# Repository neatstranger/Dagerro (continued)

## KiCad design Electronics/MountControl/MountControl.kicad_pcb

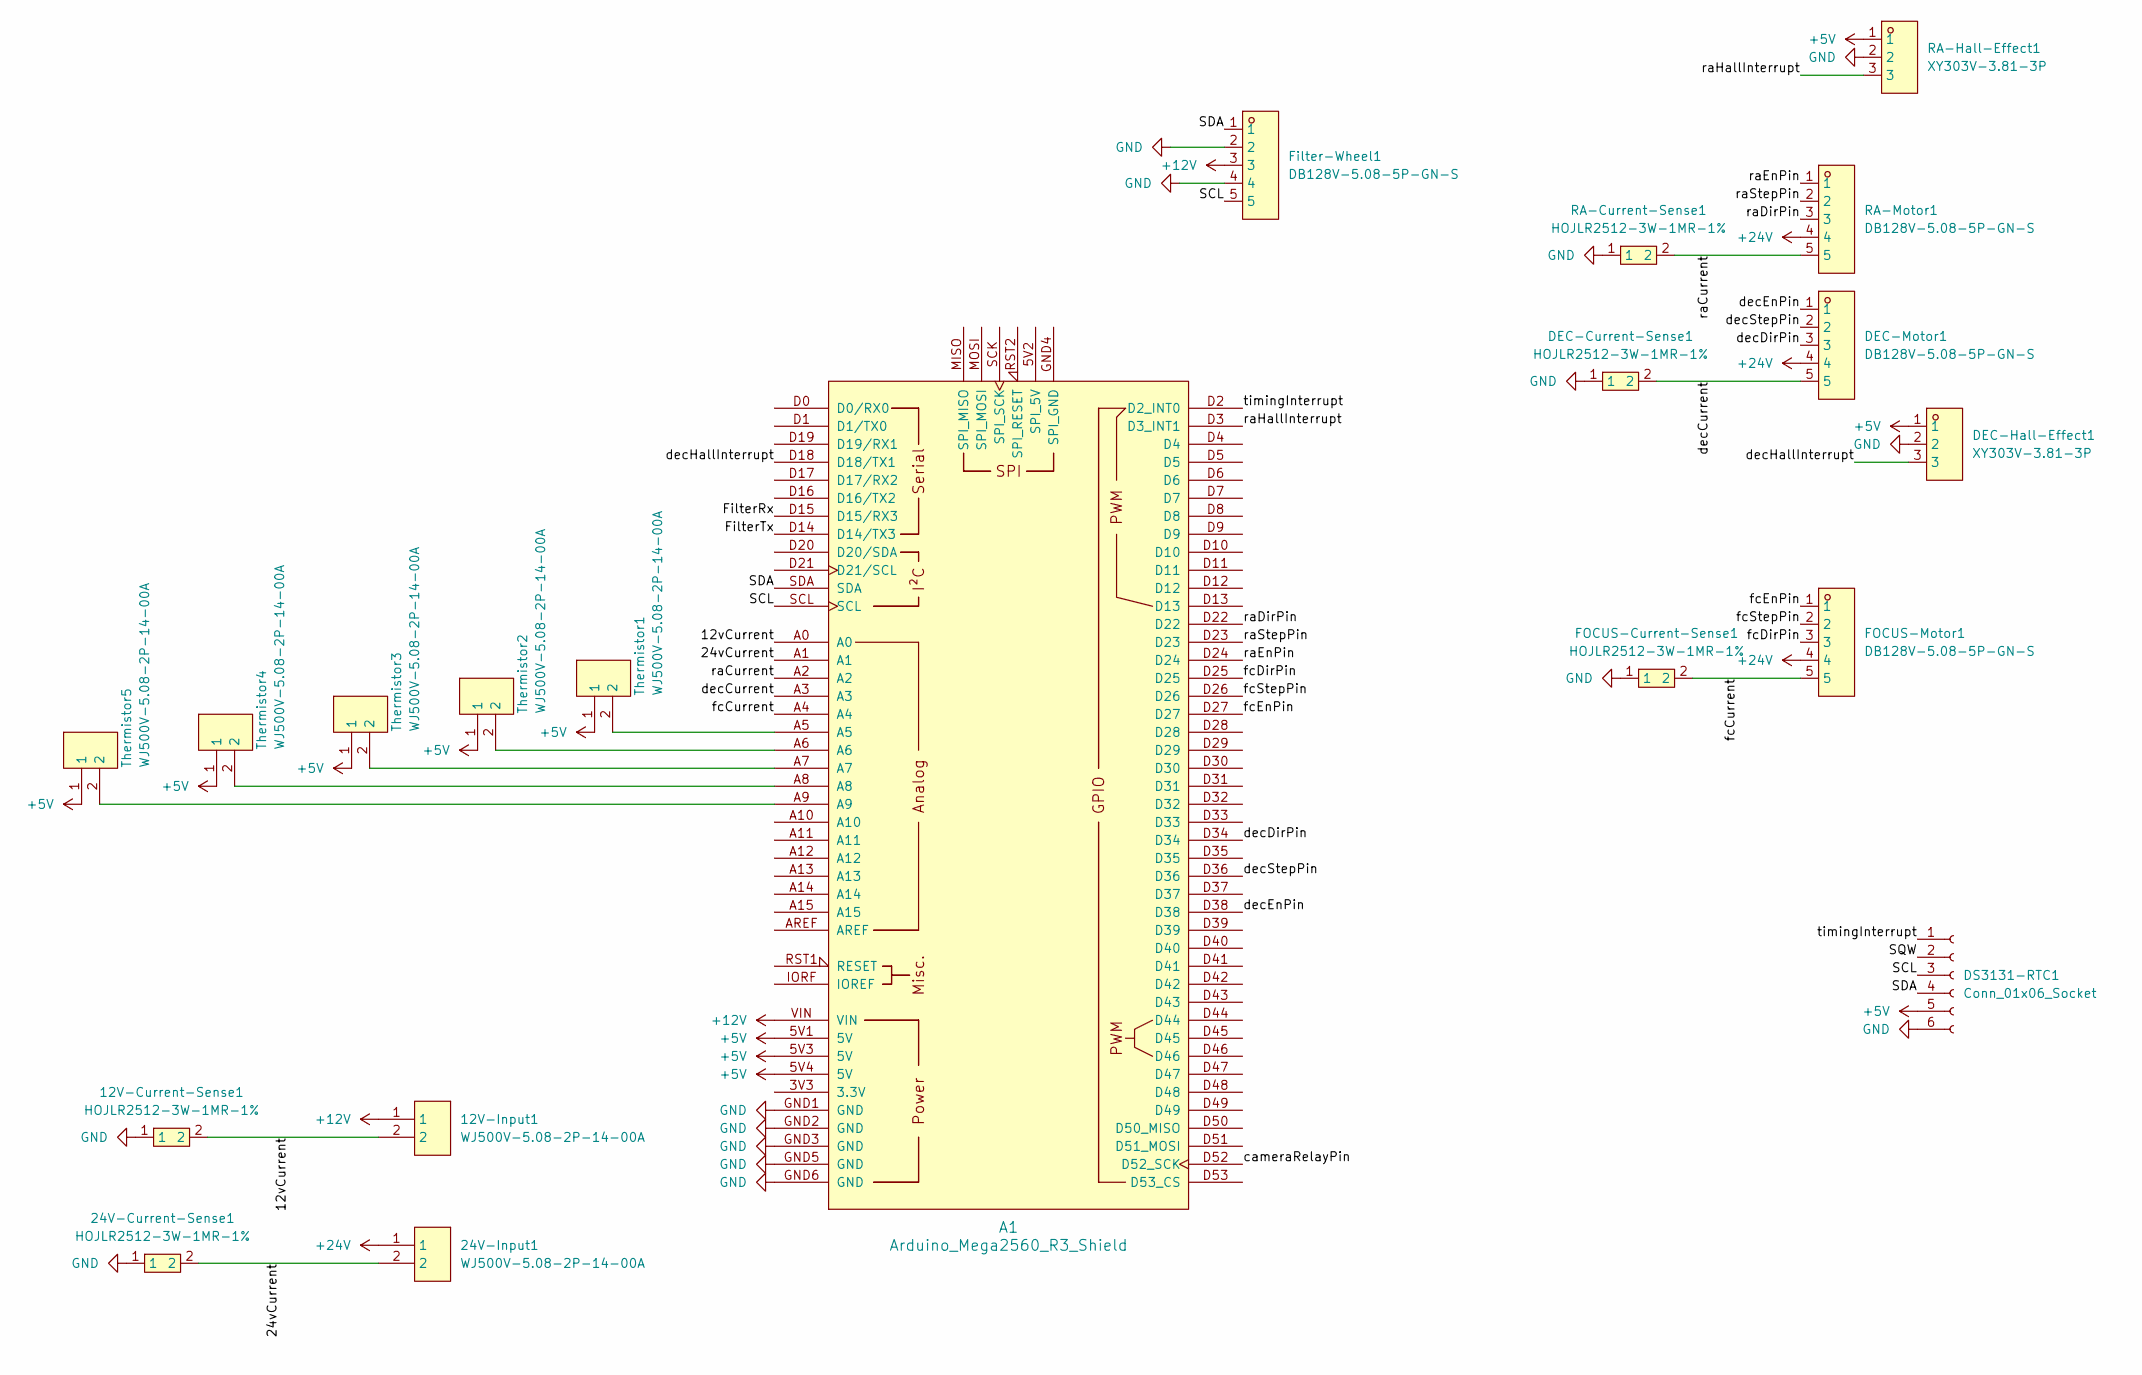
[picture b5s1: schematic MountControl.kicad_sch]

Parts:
12V-Current-Sense1, 24V-Current-Sense1: HOJLR2512-3W-1MR-1%; RES-SMD_L6.4-W3.2-R2512; LCSC Part C2903470
12V-Input1, 24V-Input1: WJ500V-5.08-2P-14-00A; CONN-TH_2P-P5.00_WJ500V-5.08-2P; LCSC Part C8465
A1: Arduino_Mega2560_R3_Shield
DEC-Current-Sense1: HOJLR2512-3W-1MR-1%; RES-SMD_L6.4-W3.2-R2512; LCSC Part C2903470
DEC-Hall-Effect1: XY303V-3.81-3P; CONN-TH_XY303V-3.81-3P; LCSC Part C557684
DEC-Motor1: DB128V-5.08-5P-GN-S; CONN-TH_5P-P5.08_DIBO_DB128V-5.08-5P-GN-S; LCSC Part C2927513
DS3131-RTC1: Conn_01x06_Socket; PinHeader_1x06_P2.54mm_Horizontal
FOCUS-Current-Sense1: HOJLR2512-3W-1MR-1%; RES-SMD_L6.4-W3.2-R2512; LCSC Part C2903470
FOCUS-Motor1: DB128V-5.08-5P-GN-S; CONN-TH_5P-P5.08_DIBO_DB128V-5.08-5P-GN-S; LCSC Part C2927513
Filter-Wheel1: DB128V-5.08-5P-GN-S; CONN-TH_5P-P5.08_DIBO_DB128V-5.08-5P-GN-S; LCSC Part C2927513
RA-Current-Sense1: HOJLR2512-3W-1MR-1%; RES-SMD_L6.4-W3.2-R2512; LCSC Part C2903470
RA-Hall-Effect1: XY303V-3.81-3P; CONN-TH_XY303V-3.81-3P; LCSC Part C557684
RA-Motor1: DB128V-5.08-5P-GN-S; CONN-TH_5P-P5.08_DIBO_DB128V-5.08-5P-GN-S; LCSC Part C2927513
Thermistor1, Thermistor2, Thermistor3, Thermistor4, Thermistor5: WJ500V-5.08-2P-14-00A; CONN-TH_2P-P5.00_WJ500V-5.08-2P; LCSC Part C8465

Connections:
+5V: A1.5V1 (5V), A1.5V3 (5V), A1.5V4 (5V), DEC-Hall-Effect1.1, DS3131-RTC1.5, RA-Hall-Effect1.1, Thermistor1.1, Thermistor2.1, Thermistor3.1, Thermistor4.1, Thermistor5.1
+12V: 12V-Input1.1, A1.VIN, Filter-Wheel1.3
+24V: 24V-Input1.1, DEC-Motor1.4, FOCUS-Motor1.4, RA-Motor1.4
/12vCurrent: 12V-Current-Sense1.2, 12V-Input1.2, A1.A0
/24vCurrent: 24V-Current-Sense1.2, 24V-Input1.2, A1.A1
/FilterRx: A1.D15 (D15/RX3)
/FilterTx: A1.D14 (D14/TX3)
/SCL: A1.SCL, DS3131-RTC1.3, Filter-Wheel1.5
/SDA: A1.SDA, DS3131-RTC1.4, Filter-Wheel1.1
/SQW: DS3131-RTC1.2
/cameraRelayPin: A1.D52 (D52_SCK)
/decCurrent: A1.A3, DEC-Current-Sense1.2, DEC-Motor1.5
/decDirPin: A1.D34, DEC-Motor1.3
/decEnPin: A1.D38, DEC-Motor1.1
/decHallInterrupt: A1.D18 (D18/TX1), DEC-Hall-Effect1.3
/decStepPin: A1.D36, DEC-Motor1.2
/fcCurrent: A1.A4, FOCUS-Current-Sense1.2, FOCUS-Motor1.5
/fcDirPin: A1.D25, FOCUS-Motor1.3
/fcEnPin: A1.D27, FOCUS-Motor1.1
/fcStepPin: A1.D26, FOCUS-Motor1.2
/raCurrent: A1.A2, RA-Current-Sense1.2, RA-Motor1.5
/raDirPin: A1.D22, RA-Motor1.3
/raEnPin: A1.D24, RA-Motor1.1
/raHallInterrupt: A1.D3 (D3_INT1), RA-Hall-Effect1.3
/raStepPin: A1.D23, RA-Motor1.2
/timingInterrupt: A1.D2 (D2_INT0), DS3131-RTC1.1
GND: 12V-Current-Sense1.1, 24V-Current-Sense1.1, A1.GND1 (GND), A1.GND2 (GND), A1.GND3 (GND), A1.GND5 (GND), A1.GND6 (GND), DEC-Current-Sense1.1, DEC-Hall-Effect1.2, DS3131-RTC1.6, FOCUS-Current-Sense1.1, Filter-Wheel1.2, Filter-Wheel1.4, RA-Current-Sense1.1, RA-Hall-Effect1.2
unnamed: A1.A5, Thermistor1.2
unnamed: A1.A6, Thermistor2.2
unnamed: A1.A7, Thermistor3.2
unnamed: A1.A8, Thermistor4.2
unnamed: A1.A9, Thermistor5.2

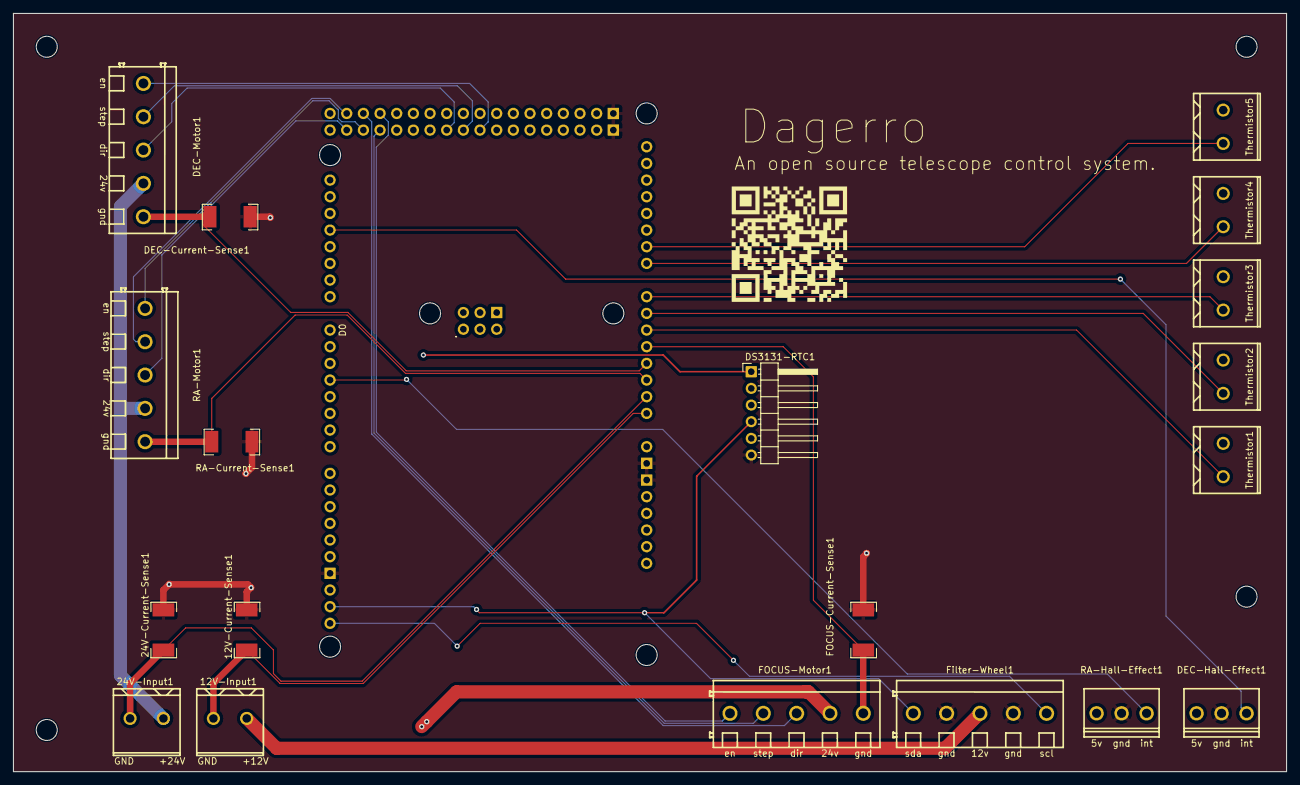
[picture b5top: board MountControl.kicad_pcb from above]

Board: 4 copper layers, 194.1 x 115.6 mm, 20 parts (0 on the bottom side), 28 nets.

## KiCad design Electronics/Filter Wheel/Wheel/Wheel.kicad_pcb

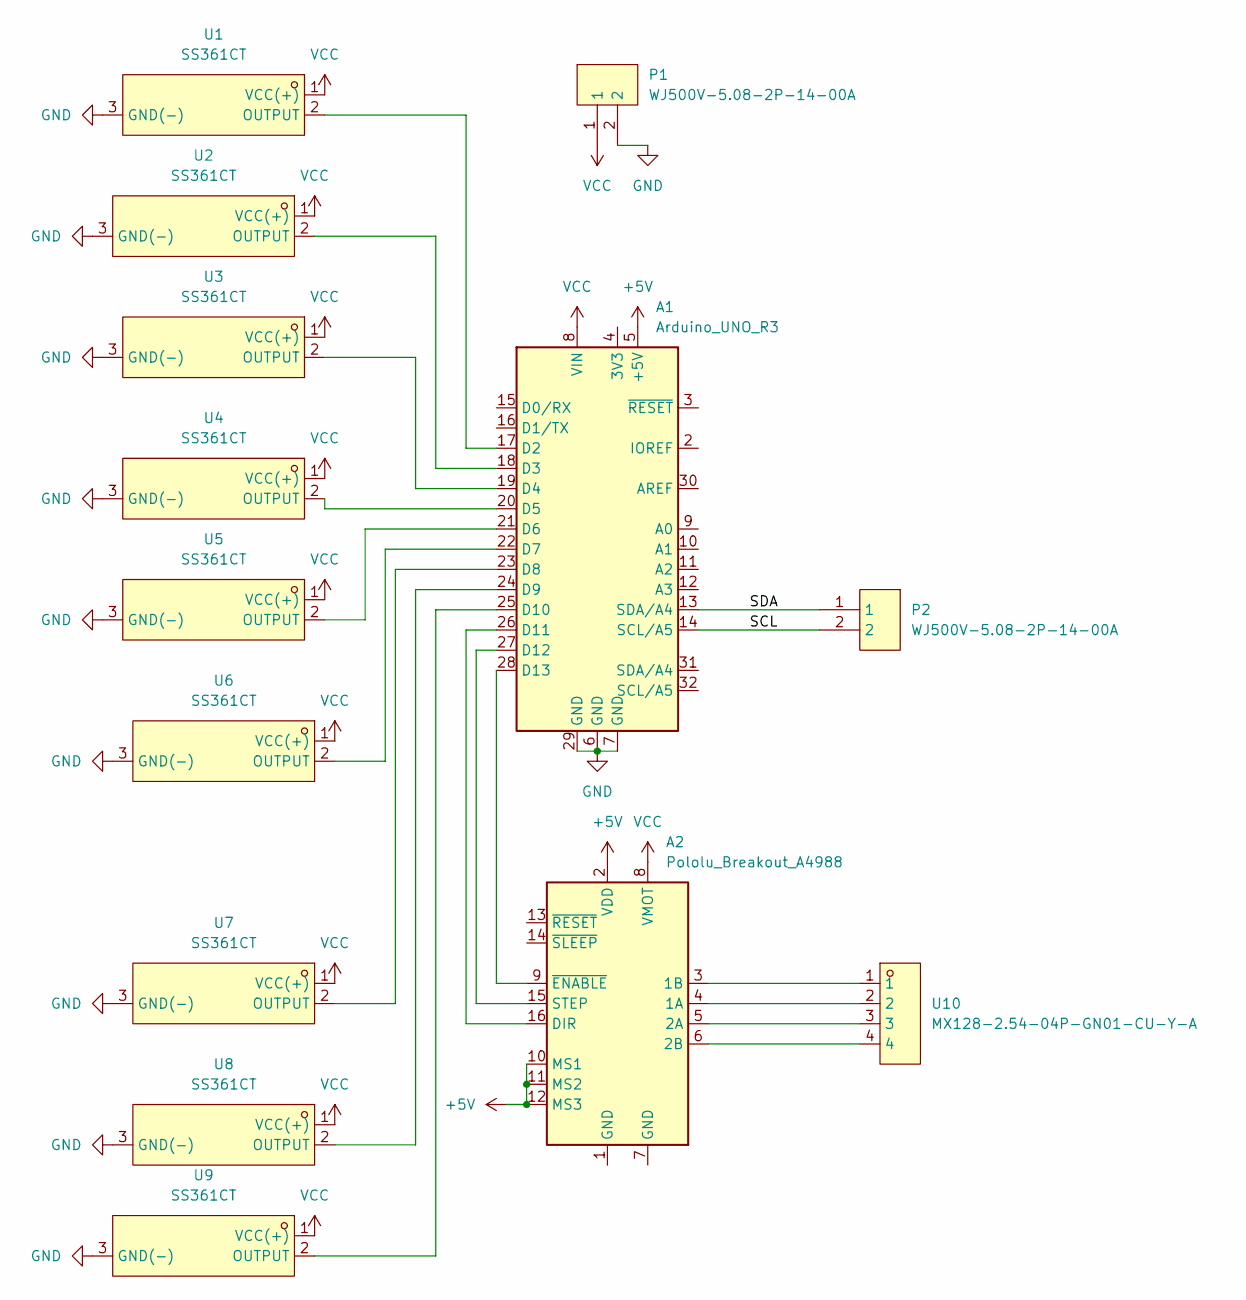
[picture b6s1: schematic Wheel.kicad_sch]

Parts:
A1: Arduino_UNO_R3
A2: Pololu_Breakout_A4988; Pololu_Breakout-16_15.2x20.3mm
P1, P2: WJ500V-5.08-2P-14-00A; CONN-TH_2P-P5.00_WJ500V-5.08-2P; LCSC Part C8465
U1, U2, U3, U4, U5, U6, U7, U8, U9: SS361CT; SOT-23-3_L2.9-W1.3-P1.90-LS2.4-BR; LCSC Part C396072
U10: MX128-2.54-04P-GN01-CU-Y-A; CONN-TH_4P-P2.54_MX128-2.54-GN01-04P-CU-Y-A; LCSC Part C5188444

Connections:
+5V: A1.5 (+5V), A2.2 (VDD), A2.10 (MS1), A2.11 (MS2), A2.12 (MS3)
/SCL: A1.14 (SCL/A5), P2.2
/SDA: A1.13 (SDA/A4), P2.1
GND: A1.6 (GND), A1.7 (GND), A1.29 (GND), P1.2, U1.3 (GND(-)), U2.3 (GND(-)), U3.3 (GND(-)), U4.3 (GND(-)), U5.3 (GND(-)), U6.3 (GND(-)), U7.3 (GND(-)), U8.3 (GND(-)), U9.3 (GND(-))
unnamed: A1.17 (D2), U1.2 (OUTPUT)
unnamed: A1.18 (D3), U2.2 (OUTPUT)
unnamed: A1.19 (D4), U3.2 (OUTPUT)
unnamed: A1.20 (D5), U4.2 (OUTPUT)
unnamed: A1.21 (D6), U5.2 (OUTPUT)
unnamed: A1.22 (D7), U6.2 (OUTPUT)
unnamed: A1.23 (D8), U7.2 (OUTPUT)
unnamed: A1.24 (D9), U8.2 (OUTPUT)
unnamed: A1.25 (D10), U9.2 (OUTPUT)
unnamed: A1.26 (D11), A2.16 (DIR)
unnamed: A1.27 (D12), A2.15 (STEP)
unnamed: A1.28 (D13), A2.9 (~ENABLE)
unnamed: A2.4 (1A), U10.2
unnamed: A2.3 (1B), U10.1
unnamed: A2.5 (2A), U10.3
unnamed: A2.6 (2B), U10.4
VCC: A1.8 (VIN), A2.8 (VMOT), P1.1, U1.1 (VCC(+)), U2.1 (VCC(+)), U3.1 (VCC(+)), U4.1 (VCC(+)), U5.1 (VCC(+)), U6.1 (VCC(+)), U7.1 (VCC(+)), U8.1 (VCC(+)), U9.1 (VCC(+))

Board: 2 copper layers, 14 parts (0 on the bottom side), 21 nets, no tracks yet.

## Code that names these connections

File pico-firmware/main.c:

#include <stdio.h>
#include <stdlib.h>
#include "pico/stdlib.h"
#include "hardware/i2c.h"

#include "i2c.h"

#define RTC_ADDR 32
#define KHZ 13
#define EN_5V 14
#define EN_CAM 15

#define EN_DEC 6
#define STEP_DEC 7
#define DIR_DEC 8

#define EN_EQ 10 
#define STEP_EQ 11
#define DIR_EQ 12

#define EN_FC 20
#define STEP_FC 19
#define DIR_FC 18


#define HOME_EQ 2
#define HOME_DEC 3

/*#define TRK_DIR 1 */
#define STEP_SLEEP_US 500



#define SMALL_CT_LOOPS 776
#define SMALL_CT_PULSES 1485

#define LG_CT_LOOPS 724
#define LG_CT_PULSES 1486

int currentInterrupts = 0;
bool onLGLoop = false;
int loops = 0;
int decComp = 100;
bool decCompDir = false;
bool decCompEnabled = false;

bool trackingEnabled = true;
bool TRK_DIR = false;


int initializeIo(){
	int controlPins[] = {EN_5V, EN_CAM, EN_DEC, STEP_DEC, DIR_DEC, EN_EQ, STEP_EQ, DIR_EQ, EN_FC, STEP_FC, DIR_FC};
	int numPins  = sizeof(controlPins) / sizeof(controlPins[0]);
	for(int i = 0; i < numPins; i++){
		printf("Initiated Pin # %d \n", controlPins[i]);
		gpio_init(controlPins[i]);
		gpio_set_dir(controlPins[i], GPIO_OUT);
	}
	gpio_init(KHZ);
	gpio_set_dir(KHZ, GPIO_IN);
	
	gpio_init(HOME_EQ);
	gpio_init(HOME_DEC);

	gpio_set_dir(HOME_EQ, GPIO_IN);
	gpio_set_dir(HOME_DEC, GPIO_IN);
	gpio_pull_up(HOME_EQ);
	gpio_pull_up(HOME_DEC);
	return 0;
		
}


int moveDecAxis(bool dir, long int steps){
	gpio_put(DIR_DEC, dir);
	busy_wait_us_32(100);
	for(long int i = 0; i < steps; i++){
		gpio_put(STEP_DEC, 1);
		busy_wait_us_32(STEP_SLEEP_US);
		gpio_put(STEP_DEC, 0);
	}
	return 0;
}
int moveEQAxis(bool dir, long int steps){
	gpio_put(DIR_EQ, dir);
	busy_wait_us_32(100);
	for(long int i = 0; i < steps; i++){
		gpio_put(STEP_EQ, 1);
		busy_wait_us_32(STEP_SLEEP_US);
		gpio_put(STEP_EQ, 0);
	}
	return 0;
}
int moveFocAxis(bool dir, long int steps){
	gpio_put(DIR_FC, dir);
	for(long int i = 0; i < steps; i++){
		gpio_put(STEP_FC, 1);
		busy_wait_us_32(STEP_SLEEP_US);
		gpio_put(STEP_FC, 0);
	}
	return 0;
}

void callBack(uint gpio, uint32_t events){
	if(trackingEnabled){
		currentInterrupts += 1;
		if(onLGLoop){
			if(currentInterrupts == LG_CT_PULSES-1){
				currentInterrupts = 0;
				moveEQAxis(TRK_DIR, 1);
				loops += 1;
				if(loops % decComp && decCompEnabled){
					moveDecAxis(decCompDir, decComp);
				}
				if(loops == LG_CT_LOOPS-1){
					onLGLoop = false;
					loops = 0;
					printf("LoopReset\n");
				}
			}
		}else{
			if(currentInterrupts == SMALL_CT_PULSES -1){
				currentInterrupts = 0;
				moveEQAxis(TRK_DIR, 1);
				loops +=1;
				if (loops % decComp && decCompEnabled){
					moveDecAxis(decCompDir, decComp);
				}
				if(loops == SMALL_CT_LOOPS -1){
					loops = 0;
					onLGLoop = true;
					printf("LoopReset \n");
				}
			}
		}
	}
}
int char_array_to_int(const char *chars, int length) {
    int result = 0;
    int is_negative = 0;
    int start = 0;

    // Check if the number is negative
    if (chars[0] == '-') {
        is_negative = 1;
        start = 1; // Start from the next character
    }

    for (int i = start; i < length; i++) {
        // Shift the result by 1 decimal place (multiply by 10)
        result = (result << 3) + (result << 1); // result * 10 using bit shifting

        // Convert the current character to its integer value and add it
        result += chars[i] - '0';
    }

    // Apply the negative sign if needed
    if (is_negative) {
        result = -result;
    }

    return result;
}
int executeMoveCommand(int eq, int dec, int fc){
	trackingEnabled = false;
	printf("Disabled Tracking For Manual Control\n......\n");
	if(eq == 0){
		printf("No EQ Command\n");
	}else if(eq != 0){
		printf("Moving EQ Axis %d steps, in the %d direction \n", abs(eq), eq > 0);
		moveEQAxis(eq > 0, abs(eq));
	}
	if(dec == 0){
		printf("No DEC Command\n");
	}else if (dec != 0){
		printf("Moving DEC Axis %d steps, in the %d direction \n", abs(dec), dec >0);
		moveDecAxis(dec > 0, abs(dec));
	}
	if(fc == 0){
		printf("No Focus Command\n");
	}else if( fc != 0){
		printf("Moving FC Axis %d steps, in the %d direction \n", abs(fc), fc >0);
		moveFocAxis(fc > 0, abs(fc));
	}

	printf(".....\nFinished all movement commands, re-enabling tracking ...\n");
	trackingEnabled = true;

	
}
int executeMachineCommand(int commandNumber){
	printf("Machine command %d  initiated \n", commandNumber);
	if(commandNumber == 1){
		printf("Disabling Steppers and Tracking\n");
		gpio_put(EN_EQ, 0);
		gpio_put(EN_DEC, 0);
		gpio_put(EN_FC, 0);
		trackingEnabled = false;
	}else if(commandNumber == 2){
		printf("Enabling All Axis");
		gpio_put(EN_EQ, 1);
		gpio_put(EN_DEC, 1);
		gpio_put(EN_FC, 1);
	}else if(commandNumber == 3){
		trackingEnabled = true;
	}else if (commandNumber ==4){
		gpio_put(EN_CAM, 0);
		sleep_ms(50);
		gpio_put(EN_CAM, 1);
	}else if (commandNumber == 5){
		TRK_DIR = !TRK_DIR;
	}else if (commandNumber == 6){
		decComp += 10;
	}else if (commandNumber == 6){
		decComp -= 10;
	}else if (commandNumber == 7){
		decCompDir = !decCompDir;
	}else if (commandNumber == 8){
		decCompEnabled = !decCompEnabled;
	}

	return 0;

}
int main(){
	stdio_init_all();
	printf("Initializing...\n");
	initializeI2C();
	initializeIo();
	gpio_put(EN_CAM, 1);
	gpio_put(EN_DEC, 1);
	gpio_put(EN_EQ, 1);
	gpio_put(EN_FC, 1);
	gpio_set_irq_enabled_with_callback(KHZ, 0x04, 1, & callBack);
	executeMachineCommand(3);
	bool messageCompleted = false;
	char message[1000];	
	int messageChar = 0;
	int cmds[3];
	printf("Tracking Enabled: %d \n", trackingEnabled);
	while(1){
		if(!gpio_get(HOME_EQ)){
			printf("EQ IS HOMED \n");
		}
		if(!gpio_get(HOME_DEC)){
			printf("DEC IS HOMED \n");
		}
		if(uart_is_readable(uart0)){
			char c = uart_getc(uart0);
			message[messageChar] = c;
			messageChar += 1;
			if(c == '\r'){
				messageCompleted = true;
				message[messageChar -1] = 0;
				messageChar = 0;
			}
		}
		if(messageCompleted && message[0] != 'G'){
			int count = 0; 
			char numArr[1000];
			int varsPulled = 0;
			for(int i = 0; i < 1000; i++){
				if(message[i] != 0 || varsPulled < 3){
					if(message[i] != ';'){
						numArr[count] = message[i];
						count++;
					}else{
						cmds[varsPulled] = char_array_to_int(numArr, count);								  varsPulled += 1;
						count = 0;
						for(int i = 0; i < 1000; i++){
							numArr[i] = 0; 
						}
					}
				}
			}	
			messageCompleted = false;
			executeMoveCommand(cmds[0], cmds[1], cmds[2]);
			for (int i = 0; i < 1000; i++){
				message[i] = 0;
			}
			cmds[0] = 0;
			cmds[1] = 0;
			cmds[2] = 0;
		}else if(messageCompleted){
			int count = 0;
			char numArr[1000];
			for (int i = 1; i < 1000; i++){
				if(message[i] != 0){
					numArr[count] = message[i];
					count++;
				}else{
					numArr[i] = message[i];
			}
		}
				
			executeMachineCommand(char_array_to_int(numArr, count));
			messageCompleted = false;
			for (int i = 0; i < 1000; i++){
				message[i] = 0;
				numArr[i] = 0;
			}


	}	

	}
    
}

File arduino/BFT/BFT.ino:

#include <DS3231.h>
DS3231 RTC;



//RTC Pins
const uint8_t timingInterruptPin = 2; //Hardware interrupt 4
//Hall Effect Sensor Pins
const uint8_t eqHallInterruptPin = 3;//Eq
const uint8_t decHallInterruptPin = 18;//Dec
//DEC Stepper Pins
const uint8_t decEnPin = 38;// Enable 22
const uint8_t decStepPin = 36;// Step 24
const uint8_t decDirPin = 34;// Direction 26
//EQ Stepper Pins
const uint8_t eqEnPin = 24;// Enable 23
const uint8_t eqStepPin = 23;// Step 25
const uint8_t eqDirPin = 22;// Direction 27
//Focus Stepper Pins
const uint8_t fcEnPin = 27;//Enable   36
const uint8_t fcStepPin = 26;//Step  34
const uint8_t fcDirPin = 25;//Direction 32
//Camera Power Disable Pin 37
const uint8_t cameraPowerPin = 52; //Camera Relay is Normally Closed.

//Serial communication variables
String serialCommand;
bool commandFinished = false;

int pulsesReceived = 0;
bool secondaryPulseCount = false;
int stepsTaken = 0;



long currentEqSteps = 0;
long maxEqSteps = 446900;

long currentDecSteps = 0;
long maxDecSteps = 223448;


void setup() {
  initializeSerialInterfaces();
  initializePinDirections();
  initializeInterruptInterfaces();
  initializeRTCModule();
  initializeAxisMotors();
}

void loop() {
  checkCommandFinished();
}




void serialEvent() {
  while (Serial.available()){
    char inChar = (char)Serial.read();
    serialCommand += inChar;
    if (inChar == ';'){
      commandFinished = true;
    }
  }
}



void initializeSerialInterfaces(){
  //Begin Serial Interfaces
  Serial.begin(115200);
  Wire.begin();
  delay(1);
  Serial.println("Serial Initialized");
}
void initializeRTCModule(){  
  RTC.enable32kHz(true);
  Serial.println("RTC Initialized");
}
void initializePinDirections(){
  //declination axis
  pinMode(decEnPin, OUTPUT);
  pinMode(decStepPin, OUTPUT);
  pinMode(decDirPin, OUTPUT);
  //equitorial axis
  pinMode(eqEnPin, OUTPUT);
  pinMode(eqStepPin, OUTPUT);
  pinMode(eqDirPin, OUTPUT);
  //focus control axis
  pinMode(fcEnPin, OUTPUT);
  pinMode(fcStepPin, OUTPUT);
  pinMode(fcDirPin, OUTPUT);
  //camera power control 
  pinMode(cameraPowerPin, OUTPUT);
  //interrupt pins
  pinMode(timingInterruptPin, INPUT);
  pinMode(eqHallInterruptPin, INPUT);
  pinMode(decHallInterruptPin, INPUT);
  Serial.println("Interface Pins Initialized");
}
void initializeInterruptInterfaces(){
  attachInterrupt(digitalPinToInterrupt(timingInterruptPin), trackingInterrupt, RISING);
}
void initializeAxisMotors(){
  digitalWrite(eqEnPin, HIGH);
  digitalWrite(decEnPin, HIGH);
  Serial.println("Motor output Enabled");
}
void checkCommandFinished(){
  if (commandFinished){
    executeCommand(serialCommand);
    clearCommand();
  }
}



void trackingInterrupt(){
  pulsesReceived += 1;
  if (pulsesReceived == 1514 && !secondaryPulseCount){
      stepsTaken += 1;
    if (stepsTaken == 48){
      stepsTaken = 0;
      secondaryPulseCount = !secondaryPulseCount;
    }
    moveEqAxis(1, false);
    pulsesReceived = 0;
  }
  else if (pulsesReceived == 1513 && secondaryPulseCount){
    stepsTaken += 1;
    if (stepsTaken == 48){
      stepsTaken = 0;
      secondaryPulseCount = !secondaryPulseCount;
    }
    moveEqAxis(1, false);
    pulsesReceived = 0;
  }
}

void executeCommand(String command){
  Serial.println("Receiving Manual Update Command. Disabling RTC Interrupt Pulses");
  RTC.enable32kHz(false);
  String commandType = command.substring(0,1);
  long movement = command.substring(1).toInt();
  bool direction = (movement > 0);
  long steps = arcSecsToSteps(abs(movement));
  String dir = String("LOW");
  if (direction){
    dir = String("HIGH");
  }
  if(commandType == "D"){
    Serial.println("Declination Axis Move: "+ String(steps) +", Direction: "+String(dir));
    moveDecAxis(steps, direction);
  }
  if(commandType == "E"){
    Serial.println("Equitorial Axis Move: "+ String(steps)+", Direction: "+String(dir));
    moveEqAxis(steps, direction);
  }
  if(commandType == "F"){
    Serial.println("Focus Move: "+ String(movement)+", Direction: "+String(dir));
    moveFcAxis(abs(movement), direction);
  }
  if(commandType == "G"){
    Serial.println("Interpreting General Command");
    executeGeneralCommand(movement);
   }
  Serial.println("Finished Mnual Command, Enabling RTC Interrupt Pulses");
  RTC.enable32kHz(true);
}



void clearCommand(){
  serialCommand = "";
  commandFinished = false;
}

void moveEqAxis(long steps, bool direction){
  digitalWrite(eqDirPin, direction);
  long i = 0;
  while (i < steps){
    if(abs(currentEqSteps) <= maxEqSteps){
      digitalWrite(eqStepPin, HIGH);
      delayMicroseconds(160);
      digitalWrite(eqStepPin, LOW);
      delayMicroseconds(160);
      if(direction){
        currentEqSteps += 1;
      }else{
        currentEqSteps -= 1;
      }
      i++;
    }else{
      i = steps;
      Serial.println("End of ability to move on Equitorial Axis. Unable to Move Further.");
    }
  }
  if(steps > 1){
    Serial.println("Completed Equitorial Move. Current Pos: "+String(currentEqSteps));
  }
}

void moveDecAxis(long steps, bool direction){
  digitalWrite(decDirPin, direction);
  long i = 0;
  while (i < steps){
    if(abs(currentDecSteps) <= maxDecSteps){
      digitalWrite(decStepPin, HIGH);
      delayMicroseconds(160);
      digitalWrite(decStepPin, LOW);
      delayMicroseconds(160);
      if(direction){
        currentDecSteps += 1;
      }else{
        currentDecSteps -= 1;
      }
      i++;
    }else{
      i = steps;
      Serial.println("End of ability to move on Declination Axis. Unable to Move Further.");
    }
  }
  if(steps > 1){
    Serial.println("Completed Declination Move. Current Pos: "+ String(currentDecSteps));
  }
}

void moveFcAxis(long steps, bool direction){
  digitalWrite(fcEnPin, HIGH);
  digitalWrite(fcDirPin, direction);
  long i = 0;
  while (i < steps){
    digitalWrite(fcStepPin, HIGH);
    delayMicroseconds(160);
    digitalWrite(fcStepPin, LOW);
    delayMicroseconds(160);
    i++;
  }
  digitalWrite(fcEnPin, LOW);
}
void executeGeneralCommand(long commandCode){
  if (commandCode == 1){
    Serial.println("RESETTING CAMERA");
    digitalWrite(cameraPowerPin, HIGH);
    delay(5000);
    digitalWrite(cameraPowerPin, LOW);
  }
  if (commandCode == 2){
    Serial.println("Disabling RTC Pulses");
    RTC.enable32kHz(false);
  }
  if (commandCode == 3){
    Serial.println("Enabling RTC Pulses");
    RTC.enable32kHz(true);
  }
}

long arcSecsToSteps(long arcSeconds){
  const double arcSecondsPerStep = 0.725;
  long steps = arcSeconds / arcSecondsPerStep;
  return steps;
}

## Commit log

2023-09-29 First push
2023-09-29 †eest
2023-10-02 Working.
2023-10-02 Switched back to /256
2023-10-02 Hotfix
    These changes made it work for my capture session.
2023-10-02 Working on timing test.
2023-10-02 Relatively Accurate.
2023-10-02 Think I got this working correctly. Now to test.
2023-10-02 RTC 32K Tracking
    The DS3231 RTC tracks time extremely well.
    Now, instead of relying on a baseless assumption of time, we will use an exact whole number of pulses.
    We know that for MicroStep1/128, we need to take exactly 100 steps every 25.3125 Seconds.
    We receive 65,536 signals per second (on/off) from our RTC.
    So, we take 60 steps, timed at 16, 588 changes to our interrupt pin.
    And 40 steps, timed at 16,590 changes to our interrupt pin.
2023-10-02 Removing Testing Examples.
2023-10-02 Removed Unused Info.
2023-10-02 Added Schematic For Motor Driver Layout
2023-10-02 Replaced Schematic
2023-10-02 Added Gerber FIles
2023-10-02 Update README.md
    Added Schematic and Images
2023-10-03 Cycle Tracking - Movements
    Stop counting cycles, and reset cycles once updates have been completed.
2023-10-03 Added Interrupt skipping.
2023-10-03 Working on field solving and image gathering.
2023-10-03 Test images
2023-10-04 Removed clutter.
2023-10-04 Added description of how the mount tracks movement.
2023-10-04 First test.
2023-10-05 Updating calculations
2023-10-05 Updated Earths Rotational Speed
    No longer 1 Arcsec/Sec(WRONG)
    Now 15 ArcSec/Sec.
2023-10-05 Moving things around.
2023-10-05 First push.
2023-10-05 Field solve export.
2023-10-06 These camands are trash, but should work with a functional mount
2023-10-06 Moved Turn on Of 32K Pin
    Moved to end of initialization, so it can continue.
2023-10-06 Spelling mistake.
2023-10-06 Changed Pins.
2023-10-06 Okay, tracking should be working now.
2023-10-07 Added Current Limiting to Reduce Temperatures.
2023-10-07 Changed output direction for direct change of coordinates.
2023-10-07 Set Current Back To MAx
2023-10-08 Everything seems to be working now.
2023-10-08 Creating Python CLI Env
2023-10-08 Changing Scale For Faster Solving
2023-10-08 Print out result
2023-10-08 had to move the function around.
2023-10-08 Working on autoguiding
2023-10-08 Moving
2023-10-08 problems
2023-10-08 Working on it.
2023-10-09 Working on the flow.
2023-10-09 Changed Target
2023-10-09 Changed some things
2023-10-11 Changed Motor CS Pin
2023-10-12 Changed Names.
2023-10-15 Added Some Targets.
2023-10-15 Added Back in Send Confirmation
2023-10-15 Removed empty print line.
2023-10-15 Testing 15 Second Exposures
2023-10-16 Changed script slightly.
2023-10-16 Batched steps
2023-10-16 Changed to 5 steps per move.
2024-05-09 Added starter files.
2024-05-09 Working on serial.
2024-05-13 Fixed Pins.
2024-05-13 Enabled pinmodes.
2024-05-13 Making things as functions
2024-05-13 Working on tracking.
2024-05-13 Pulse tracking.
2024-05-13 Still working on tracking.
2024-05-14 Working on Handling max Steps Now.
2024-05-14 Initializing motors, adding feedback to serial.
2024-05-27 Working
2024-05-29 Added GCode to enable and disable rtc for tracking.
2024-05-29 Working on Loop
2024-05-29 Working on polar script.
2024-06-20 First push of mount controller project.
2024-06-20 Schematic Finished
2024-06-20 Layout almost done
2024-06-22 Finished with routing.
2024-06-23 Added production files
2024-10-10 Working on stepper driver
2024-10-13 Working on Pico Control
2024-11-03 Added basic code.
2024-11-04 Almost done with command interface.
2024-11-07 Working on commands
2024-11-09 Almost everything working
2024-11-16 Added Correct pin numbers.
2024-11-26 Updated PCB to Include Hall Sensors
2024-11-29 This should be working
2024-12-10 Added Homing
2025-03-02 Started working on driver.
2025-03-03 Added driver PCB
2025-03-03 Fixed 3D VIew
2025-03-03 Added magnetic encoder
2025-03-04 Added toupcam SDK
2025-03-04 Changed mode to software trigger.
2025-03-04 Revert "Changed mode to software trigger."
    This reverts commit 70d6acb8dd04d026f04fa6ff50efd9beda5d8489.
2025-03-27 Updated driver PCB
